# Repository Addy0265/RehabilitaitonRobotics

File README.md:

# RehabilitationRobotics
Work on Human-Gait analysis and development of an orthotic device for lower-limb orthosis.

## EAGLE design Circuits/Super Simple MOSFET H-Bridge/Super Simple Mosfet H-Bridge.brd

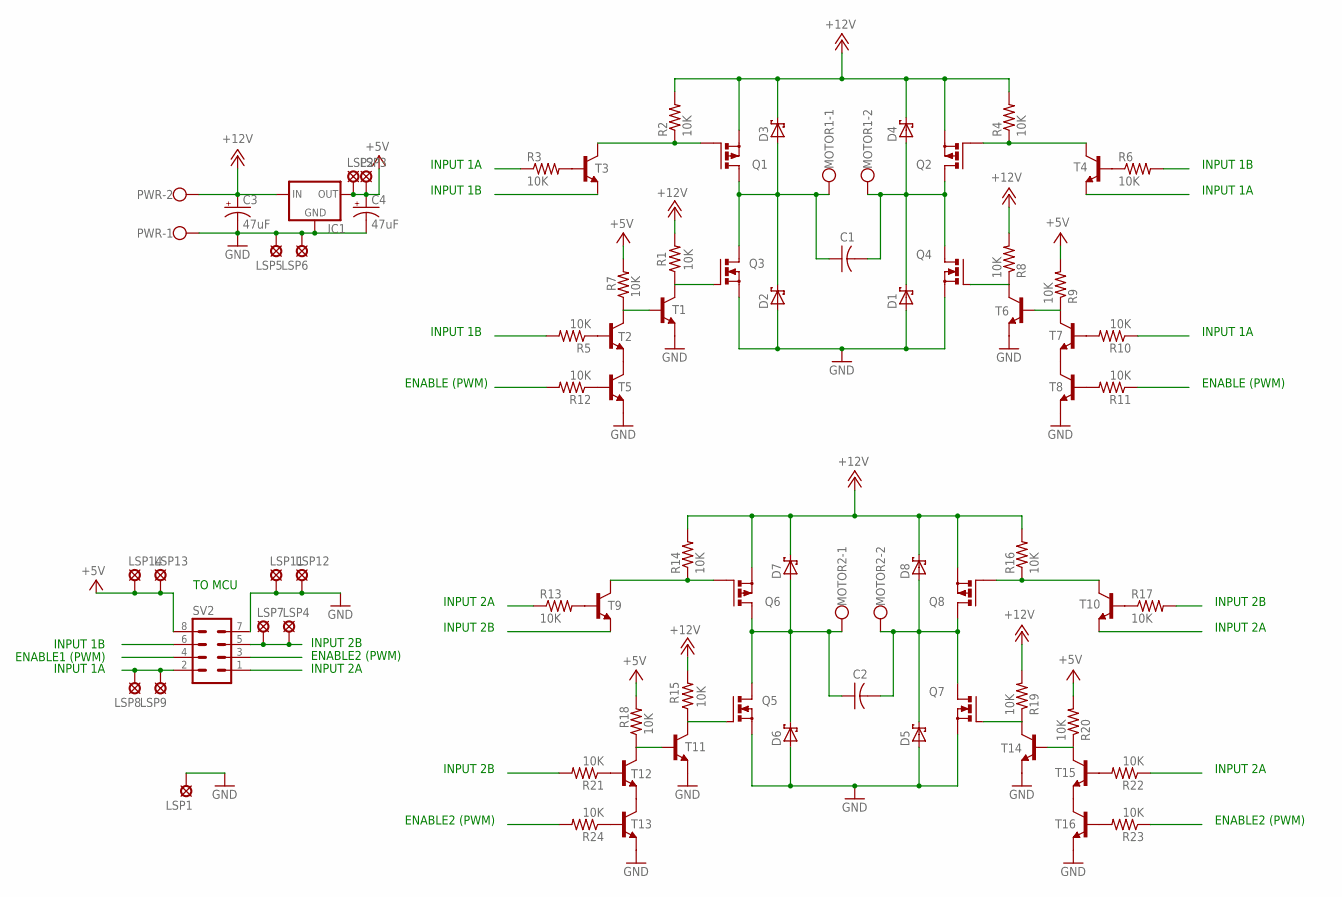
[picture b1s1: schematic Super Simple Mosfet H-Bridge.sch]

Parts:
C1, C2: C-US050-025X075; C050-025X075
C3, C4: 47uF; E2,5-6E
D1, D2, D3, D4, D5, D6, D7, D8: 1N5817-B; DO41-7.6
IC1: 78XXS
LSP1, LSP2, LSP3, LSP4, LSP5, LSP6, LSP7, LSP8, LSP9, LSP11, LSP12, LSP13, LSP14: LSP13
MOTOR1, MOTOR2: W237-102
PWR: W237-102
Q1, Q2, Q6, Q8: IRF9640; TO220BV
Q3, Q4, Q5, Q7: IRF530N; TO220BV
R1, R2, R3, R4, R5, R6, R7, R8, R9, R10, R11, R12, R13, R14, R15, R16, R17, R18, R19, R20, R21, R22, R23, R24: 10K; 0207/10
SV2: MA04-2
T1, T2, T3, T4, T5, T6, T7, T8, T9, T10, T11, T12, T13, T14, T15, T16: -NPN-TO92-EBC; TO92-EBC

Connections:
1A: LSP8.MP, LSP9.MP, R3.1, R10.1, SV2.2, T4.E
1B: R5.2, R6.2, SV2.6, T3.E
2A: R13.1, R22.1, SV2.1, T10.E
2B: LSP4.MP, LSP7.MP, R17.2, R21.2, SV2.5, T9.E
+5V: C4.+, IC1.OUT, LSP2.MP, LSP3.MP, LSP13.MP, LSP14.MP, R7.2, R9.2, R18.2, R20.2, SV2.8
+12V: C3.+, D3.C, D4.C, D7.C, D8.C, IC1.IN, PWR.2, Q1.S, Q2.S, Q6.S, Q8.S, R1.2, R2.2, R4.2, R8.2, R14.2, R15.2, R16.2, R19.2
ENABLE1: R11.1, R12.2, SV2.4
ENABLE2: R23.1, R24.2, SV2.3
GND: C3.-, C4.-, D1.A, D2.A, D5.A, D6.A, IC1.GND, LSP1.MP, LSP5.MP, LSP6.MP, LSP11.MP, LSP12.MP, PWR.1, Q3.S, Q4.S, Q5.S, Q7.S, SV2.7, T1.E, T5.E, T6.E, T8.E, T11.E, T13.E, T14.E, T16.E
unnamed: R3.2, T3.B
unnamed: Q1.G, R2.1, T3.C
unnamed: C1.1, D2.C, D3.A, MOTOR1.1, Q1.D, Q3.D
unnamed: Q2.G, R4.1, T4.C
unnamed: R6.1, T4.B
unnamed: Q3.G, R1.1, T1.C
unnamed: C1.2, D1.C, D4.A, MOTOR1.2, Q2.D, Q4.D
unnamed: R7.1, T1.B, T2.C
unnamed: T2.E, T5.C
unnamed: Q4.G, R8.1, T6.C
unnamed: R9.1, T6.B, T7.C
unnamed: Q6.G, R14.1, T9.C
unnamed: T7.E, T8.C
unnamed: C2.1, D6.C, D7.A, MOTOR2.1, Q5.D, Q6.D
unnamed: Q8.G, R16.1, T10.C
unnamed: C2.2, D5.C, D8.A, MOTOR2.2, Q7.D, Q8.D
unnamed: R13.2, T9.B
unnamed: R17.1, T10.B
unnamed: Q5.G, R15.1, T11.C
unnamed: R18.1, T11.B, T12.C
unnamed: R5.1, T2.B
unnamed: R10.2, T7.B
unnamed: R11.2, T8.B
unnamed: R12.1, T5.B
unnamed: T12.E, T13.C
unnamed: Q7.G, R19.1, T14.C
unnamed: R20.1, T14.B, T15.C
unnamed: T15.E, T16.C
unnamed: R21.1, T12.B
unnamed: R22.2, T15.B
unnamed: R23.2, T16.B
unnamed: R24.1, T13.B

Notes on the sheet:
INPUT 1A
INPUT 1B
ENABLE (PWM)
INPUT 2A
INPUT 2B
ENABLE2 (PWM)
TO MCU
ENABLE1 (PWM)

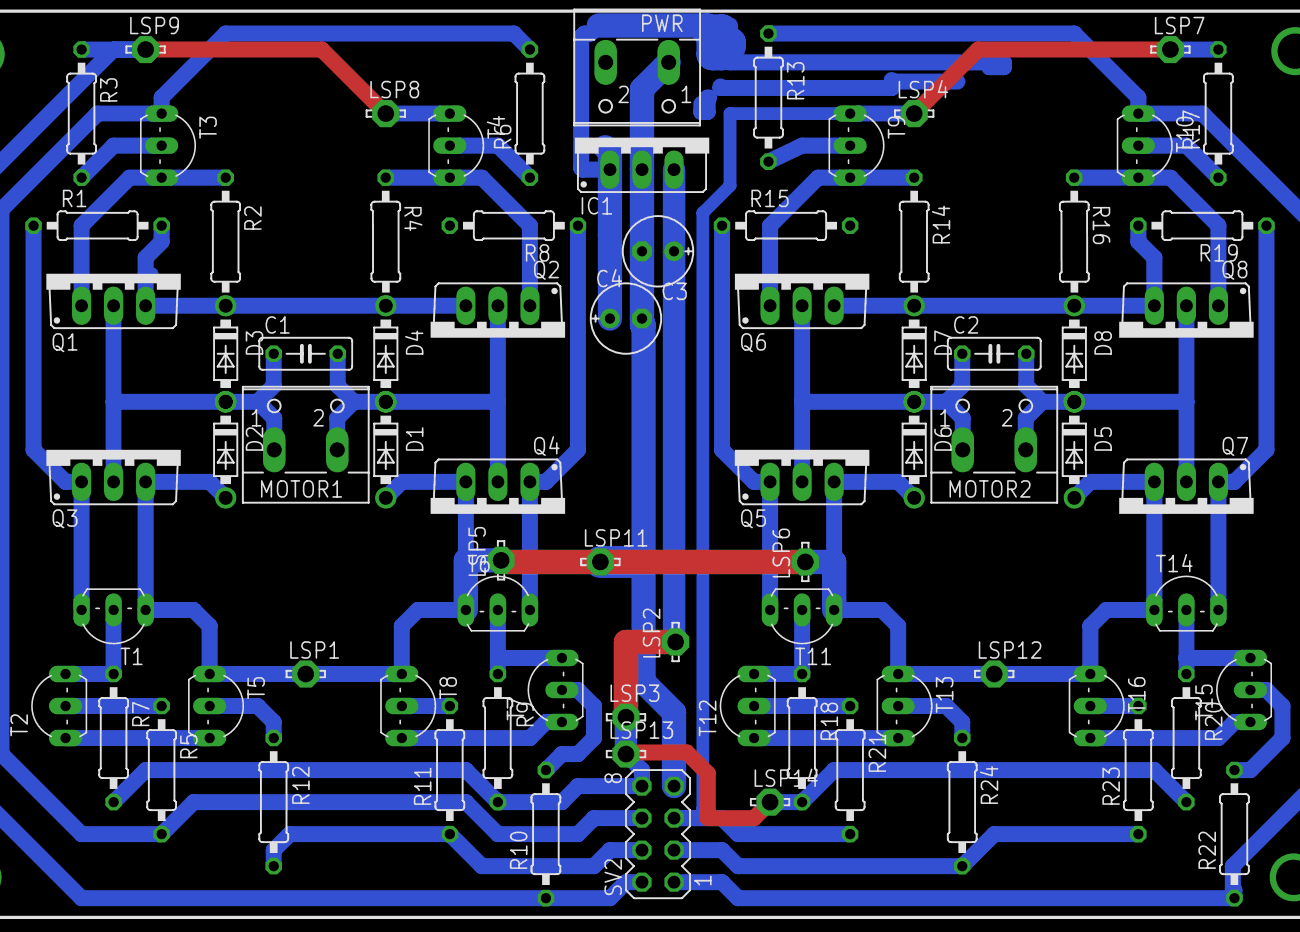
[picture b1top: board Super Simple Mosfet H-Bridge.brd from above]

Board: 2 copper layers, 78 parts (0 on the bottom side), 41 nets.

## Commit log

2017-12-13 All data added
